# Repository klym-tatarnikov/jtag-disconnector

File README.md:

# jtag-disconnector
Debug probe disconnector. <br/>
This adapater designed for power measurement, debug (deep-)sleep and low power modes on battery powered devices such as Bluetooth Low Energy, Zigbee, LoRa, etc.<br />
Normally for measuring power consumption of low power devices debug probe needs to be fully disconnected to exclude all parasitic current sources/sinks. <br />
Switching is carried out using 5V reed relays. Controlled by toggle switch or external trigger. <br />
PIN20 of JTAG connector can be used for powering device as well as to control relays. 

## Schematics

## J-Link connection

## Segger J_Link EDU-Mini connection

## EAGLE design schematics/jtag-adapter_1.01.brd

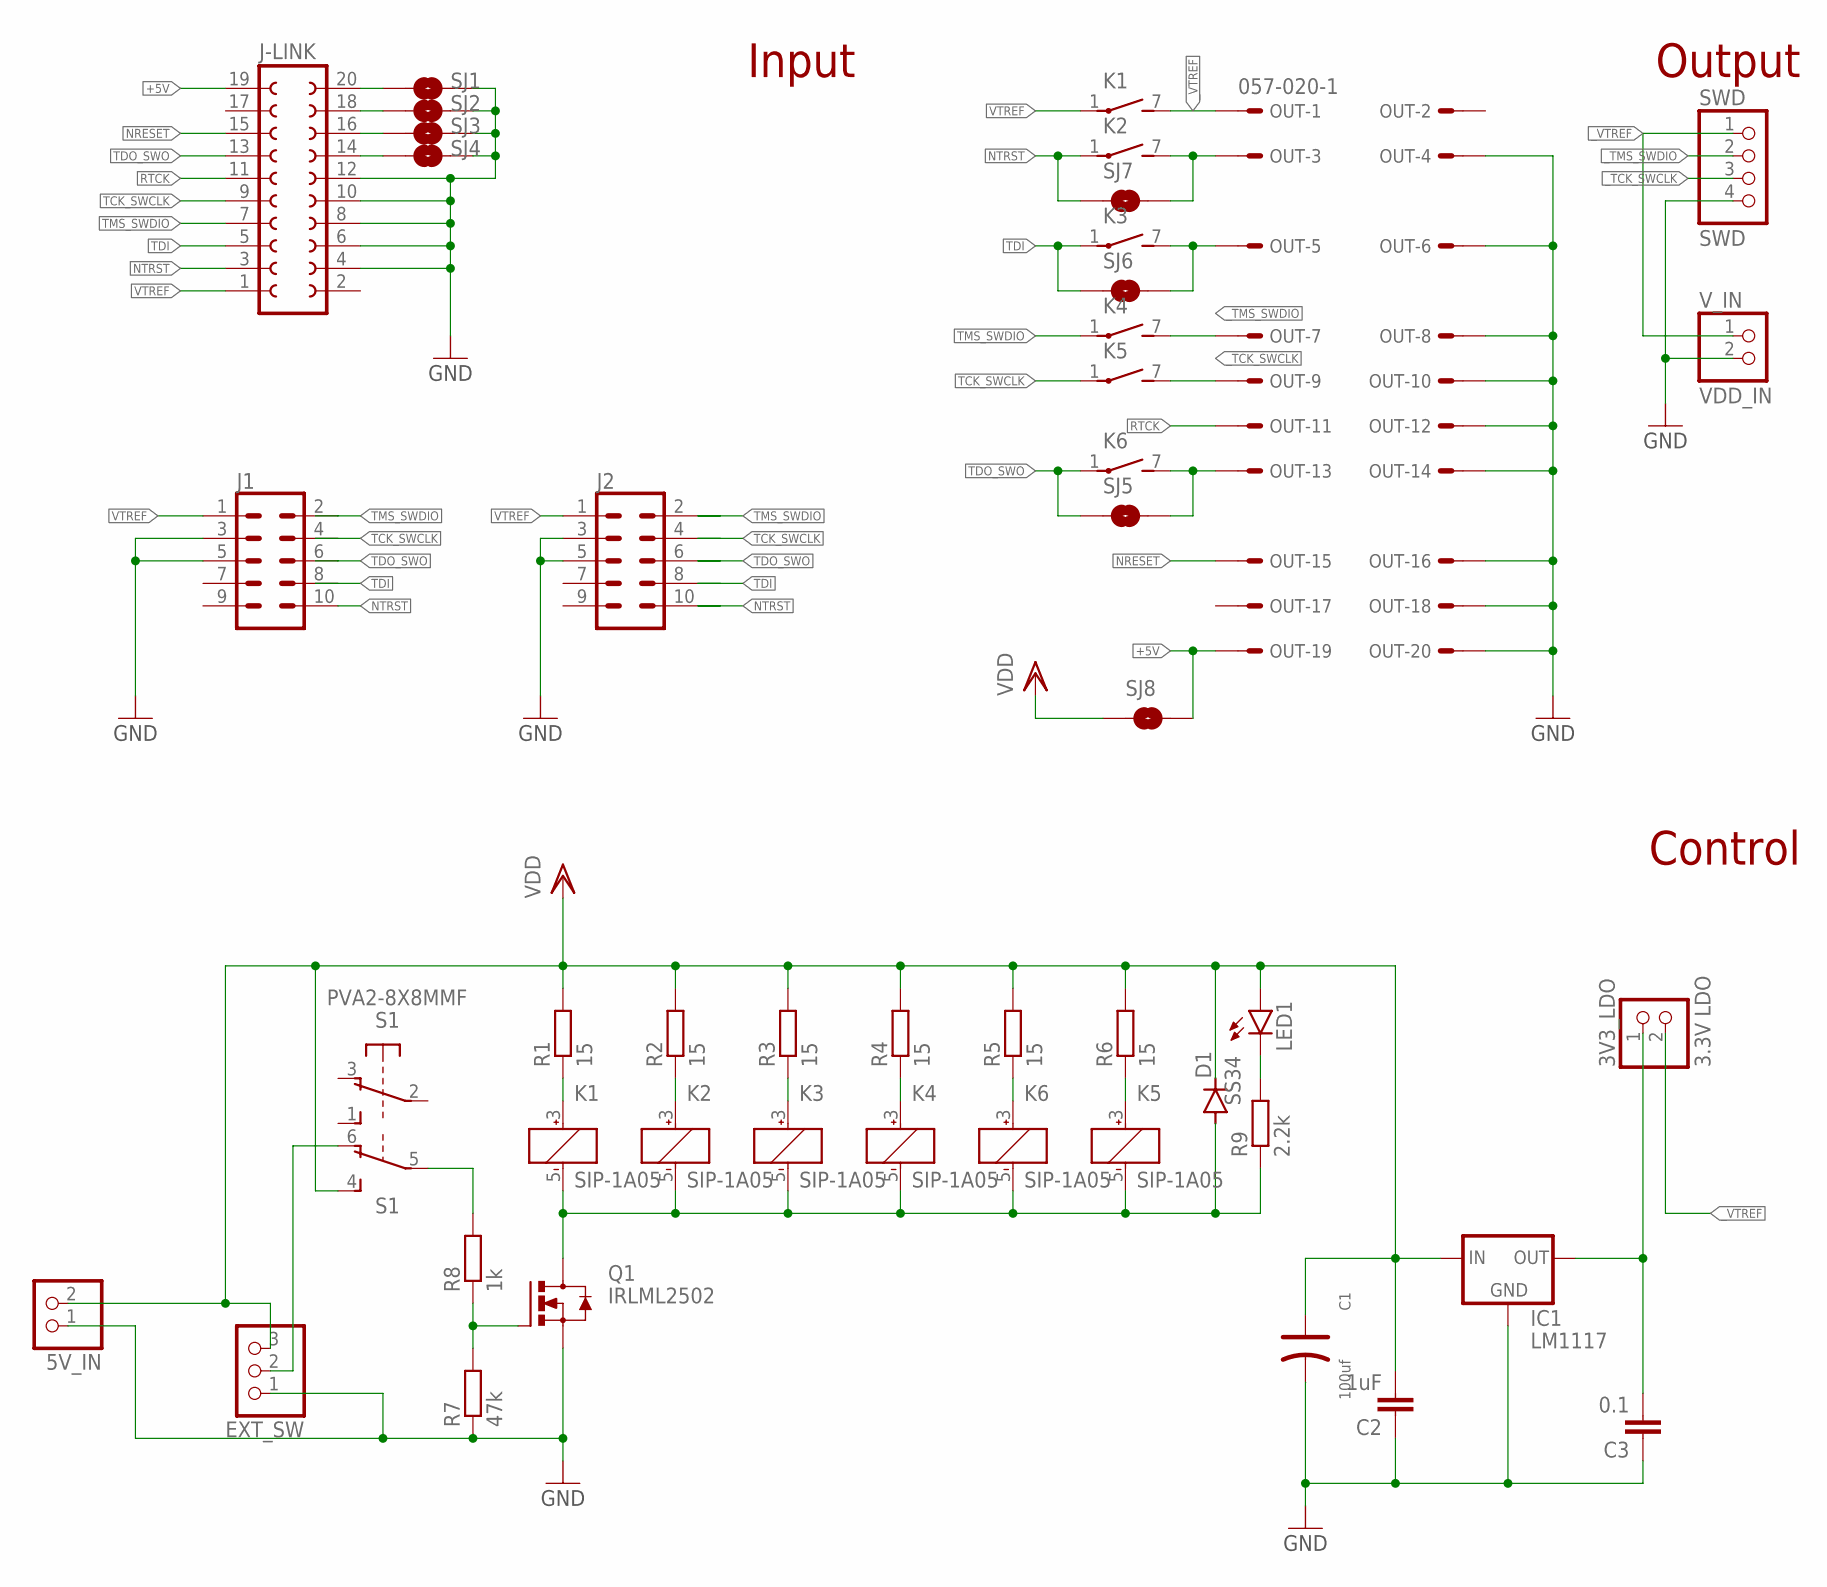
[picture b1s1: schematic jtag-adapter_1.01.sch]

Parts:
3V3_LDO: 3.3V LDO; 1X02
5V_IN: PINHD-1X2; 1X02
C1: 100uf; AVX-B
C2: 1uF; C1206
C3: 0.1; C1206
D1: SS34; SMB
EXT_SW: PINHD-1X3; 1X03
IC1: LM1117; SOT223
J1, J2: CONN_05X20.05_IN_PTH_SILK; 2X5_PTH_SILK_.05
J-LINK: FE10-2W
K1, K2, K3, K4, K5, K6: SIP-1A05; REED
LED1: LEDCHIP-LED0805; CHIP-LED0805
OUT: 057-020-1
Q1: IRLML2502; SOT23
R1, R2, R3, R4, R5, R6: 15; R0805
R7: 47k; R0805
R8: 1k; R0805
R9: 2.2k; R0805
S1: PVA2-8X8MMF; PVA2F
SJ1, SJ2, SJ3, SJ4, SJ5, SJ6, SJ7, SJ8: SOLDERJUMPERTRACE; SJ_2S-TRACE
SWD: SWD; 1X04
V_IN: VDD_IN; 1X02

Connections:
3V3_OUT: 3V3_LDO.1, C3.2, IC1.2 (OUT)
+5V: J-LINK.19, OUT.19, SJ8.2
GND: 5V_IN.1, C1.-, C2.1, C3.1, EXT_SW.1, IC1.1 (GND), J1.3, J1.5, J2.3, J2.5, J-LINK.4, J-LINK.6, J-LINK.8, J-LINK.10, J-LINK.12, OUT.4, OUT.6, OUT.8, OUT.10, OUT.12, OUT.14, OUT.16, OUT.18, OUT.20, Q1.2 (S), R7.1, SJ1.2, SJ2.2, SJ3.2, SJ4.2, SWD.4, V_IN.2
unnamed: LED1.C, R9.2
unnamed: R8.2, S1.5
unnamed: K2.7 (S), OUT.3, SJ7.2
unnamed: K3.7 (S), OUT.5, SJ6.2
unnamed: EXT_SW.2, S1.6 (O)
unnamed: K6.7 (S), OUT.13, SJ5.2
unnamed: K1.3 (+), R1.1
unnamed: K2.3 (+), R2.1
unnamed: K3.3 (+), R3.1
unnamed: K4.3 (+), R4.1
unnamed: K6.3 (+), R5.1
unnamed: K5.3 (+), R6.1
unnamed: Q1.1 (G), R7.2, R8.1
unnamed: D1.A, K1.5 (-), K2.5 (-), K3.5 (-), K4.5 (-), K5.5 (-), K6.5 (-), Q1.3 (D), R9.1
unnamed: J-LINK.14, SJ4.1
unnamed: J-LINK.16, SJ3.1
unnamed: J-LINK.18, SJ2.1
unnamed: J-LINK.20, SJ1.1
NRESET: J-LINK.15, OUT.15
NTRST: J1.10, J2.10, J-LINK.3, K2.1, SJ7.1
RTCK: J-LINK.11, OUT.11
TCK_SWCLK: J1.4, J2.4, J-LINK.9, K5.1
TDI: J1.8, J2.8, J-LINK.5, K3.1, SJ6.1
TDO_SWO: J1.6, J2.6, J-LINK.13, K6.1, SJ5.1
TMS_SWDIO: J1.2, J2.2, J-LINK.7, K4.1
VDD: 5V_IN.2, C1.+, C2.2, D1.C, EXT_SW.3, IC1.3 (IN), LED1.A, R1.2, R2.2, R3.2, R4.2, R5.2, R6.2, S1.4 (S), SJ8.1
VTREF: J1.1, J2.1, J-LINK.1, K1.1
_TCK_SWCLK: K5.7 (S), OUT.9, SWD.3
_TMS_SWDIO: K4.7 (S), OUT.7, SWD.2
_VTREF: 3V3_LDO.2, K1.7 (S), OUT.1, SWD.1, V_IN.1

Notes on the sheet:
Input
Output
Control

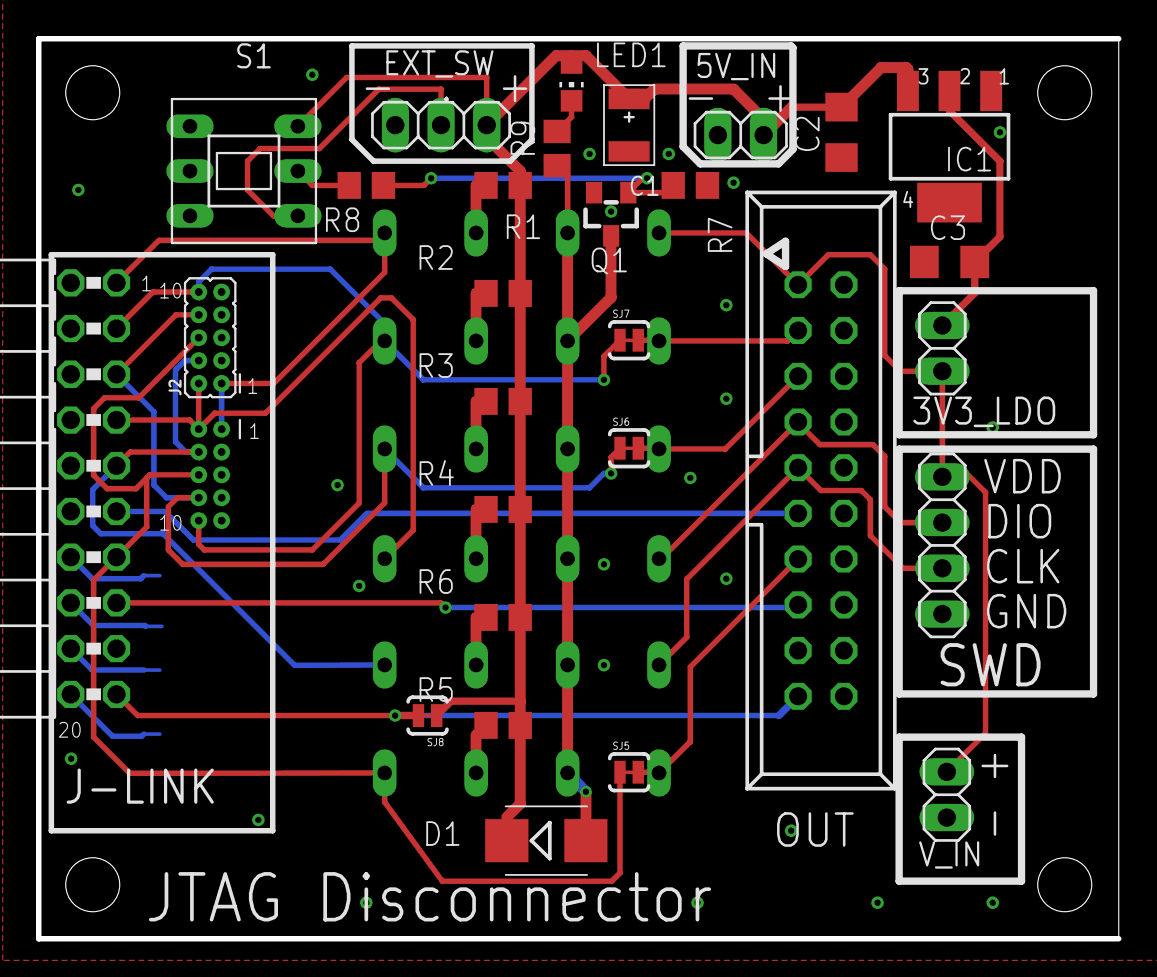
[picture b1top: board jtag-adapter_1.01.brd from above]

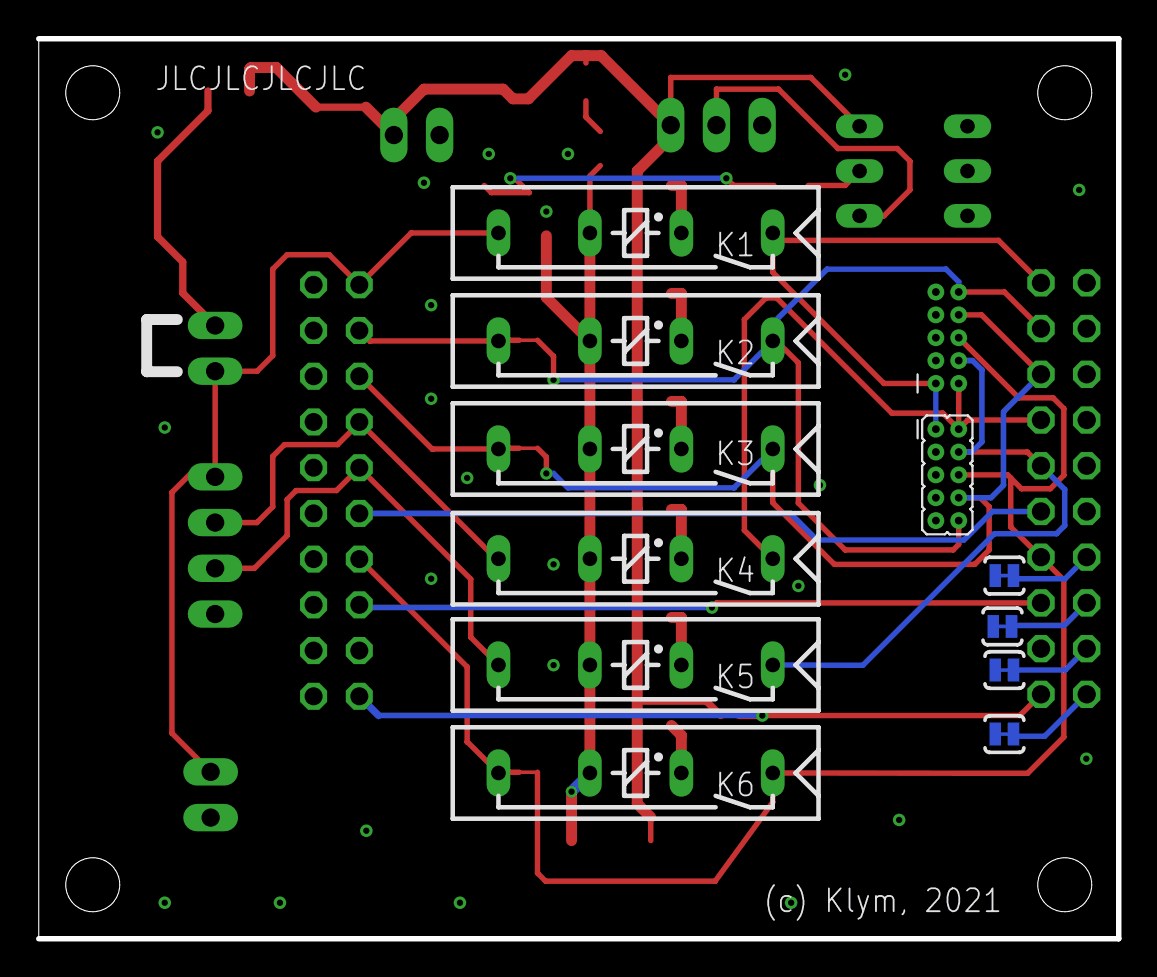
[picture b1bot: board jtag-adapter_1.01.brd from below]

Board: 2 copper layers, 60.0 x 50.0 mm, 40 parts (11 on the bottom side), 33 nets.

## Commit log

2021-08-12 Initial
2021-08-12 Readme update

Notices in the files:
parts and their libraries:
SparkFun-Connectors: Licensing: Creative Commons ShareAlike 4.0 International - https://creativecommons.org/licenses/by-sa/4.0
SparkFun: Licensing: CC v3.0 Share-Alike You are welcome to use this library for commercial purposes.
m-pad-2.1: License : GNU General Public License version 2 (see bottom)
